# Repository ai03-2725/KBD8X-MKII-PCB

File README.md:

# KBD8X-MKII-PCB
This is the source for the PCB used in the [KBD8X MKII by KBDfans](https://kbdfans.com/collections/kbd8x-mkii/products/coming-soon-kbd8x-mkii-custom-mechanical-keyboard-kit).  

Please verify the conditions of the [license](https://github.com/ai03-2725/KBD8X-MKII-PCB/blob/master/LICENSE) before using.

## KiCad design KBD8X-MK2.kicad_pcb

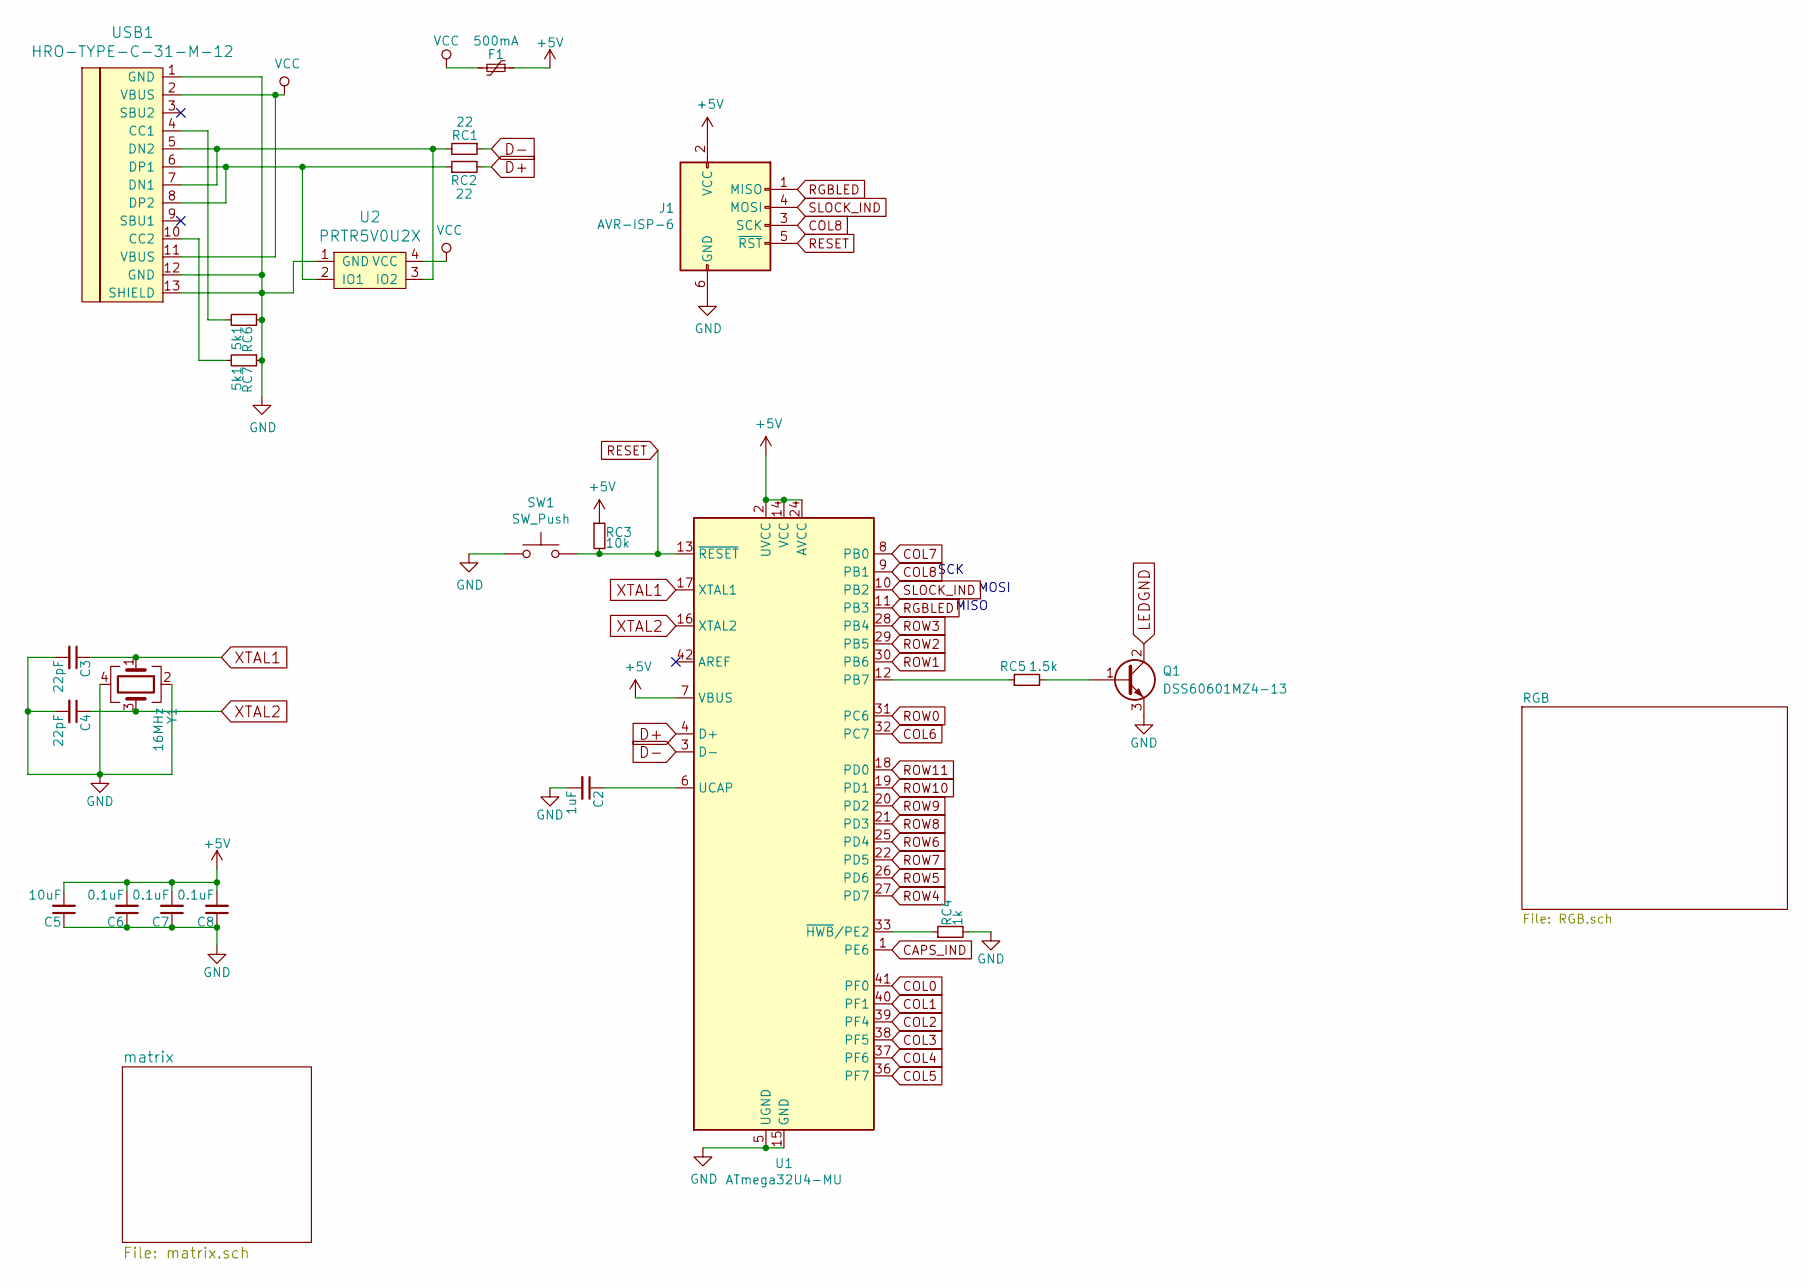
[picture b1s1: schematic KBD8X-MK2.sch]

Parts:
C2: 1uF; C_0603
C3, C4: 22pF; C_0603
C5: 10uF; C_0603
C6, C7, C8: 0.1uF; C_0603
F1: 500mA; Fuse_SMD1206_Wave
J1: AVR-ISP-6; Reset_Pretty-Mask
Q1: DSS60601MZ4-13; SOT-223-3_TabPin2
RC1, RC2: 22; R_0603
RC3: 10k; R_0603
RC4: 1k; R_0603
RC5: 1.5k; R_0603
RC6, RC7: 5k1; R_0603
SW1: SW_Push; SKQG-1155865
U1: ATmega32U4-MU; QFN-44-1EP_7x7mm_Pitch0.5mm
U2: PRTR5V0U2X; SOT143B
USB1: HRO-TYPE-C-31-M-12; HRO-TYPE-C-31-M-12-Assembly
Y1: 16MHz; Crystal_SMD_3225-4pin_3.2x2.5mm

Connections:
+5V: C5.2, C6.2, C7.2, C8.2, F1.1, J1.2 (VCC), RC3.1, U1.2 (UVCC), U1.7 (VBUS), U1.14 (VCC), U1.24 (AVCC), U1.34 (VCC), U1.44 (AVCC); also elsewhere on the board
CAPS_IND: U1.1 (PE6); also elsewhere on the board
COL0: U1.41 (PF0); also elsewhere on the board
COL1: U1.40 (PF1); also elsewhere on the board
COL2: U1.39 (PF4); also elsewhere on the board
COL3: U1.38 (PF5); also elsewhere on the board
COL4: U1.37 (PF6); also elsewhere on the board
COL5: U1.36 (PF7); also elsewhere on the board
COL6: U1.32 (PC7); also elsewhere on the board
COL7: U1.8 (PB0); also elsewhere on the board
COL8: J1.3 (SCK), U1.9 (PB1); also elsewhere on the board
D+: RC2.2, U1.4 (D+)
D-: RC1.1, U1.3 (D-)
GND: C2.2, C3.2, C4.2, C5.1, C6.1, C7.1, C8.1, J1.6 (GND), Q1.3 (E), RC4.2, RC6.1, RC7.1, SW1.1, U1.5 (UGND), U1.15 (GND), U1.23 (GND), U1.35 (GND), U1.43 (GND), U1.45 (GND), U2.1 (GND), USB1.1 (GND), USB1.12 (GND), USB1.13 (SHIELD), Y1.2, Y1.4; also elsewhere on the board
LEDGND: Q1.2 (C); also elsewhere on the board
unnamed: C2.1, U1.6 (UCAP)
unnamed: Q1.1 (B), RC5.2
unnamed: RC1.2, U2.3 (IO2), USB1.5 (DN2), USB1.7 (DN1)
unnamed: RC2.1, U2.2 (IO1), USB1.6 (DP1), USB1.8 (DP2)
unnamed: RC4.1, U1.33 (~HWB~/PE2)
unnamed: RC5.1, U1.12 (PB7)
unnamed: RC6.2, USB1.4 (CC1)
unnamed: RC7.2, USB1.10 (CC2)
RESET: J1.5 (~RST), RC3.2, SW1.2, U1.13 (~RESET)
RGBLED: J1.1 (MISO), U1.11 (PB3); also elsewhere on the board
ROW0: U1.31 (PC6); also elsewhere on the board
ROW1: U1.30 (PB6); also elsewhere on the board
ROW2: U1.29 (PB5); also elsewhere on the board
ROW3: U1.28 (PB4); also elsewhere on the board
ROW4: U1.27 (PD7); also elsewhere on the board
ROW5: U1.26 (PD6); also elsewhere on the board
ROW6: U1.25 (PD4); also elsewhere on the board
ROW7: U1.22 (PD5); also elsewhere on the board
ROW8: U1.21 (PD3); also elsewhere on the board
ROW9: U1.20 (PD2); also elsewhere on the board
ROW10: U1.19 (PD1); also elsewhere on the board
ROW11: U1.18 (PD0); also elsewhere on the board
SLOCK_IND: J1.4 (MOSI), U1.10 (PB2); also elsewhere on the board
VCC: F1.2, U2.4 (VCC), USB1.2 (VBUS), USB1.11 (VBUS)
XTAL1: C3.1, U1.17 (XTAL1), Y1.1
XTAL2: C4.1, U1.16 (XTAL2), Y1.3

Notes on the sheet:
MOSI
MISO
SCK

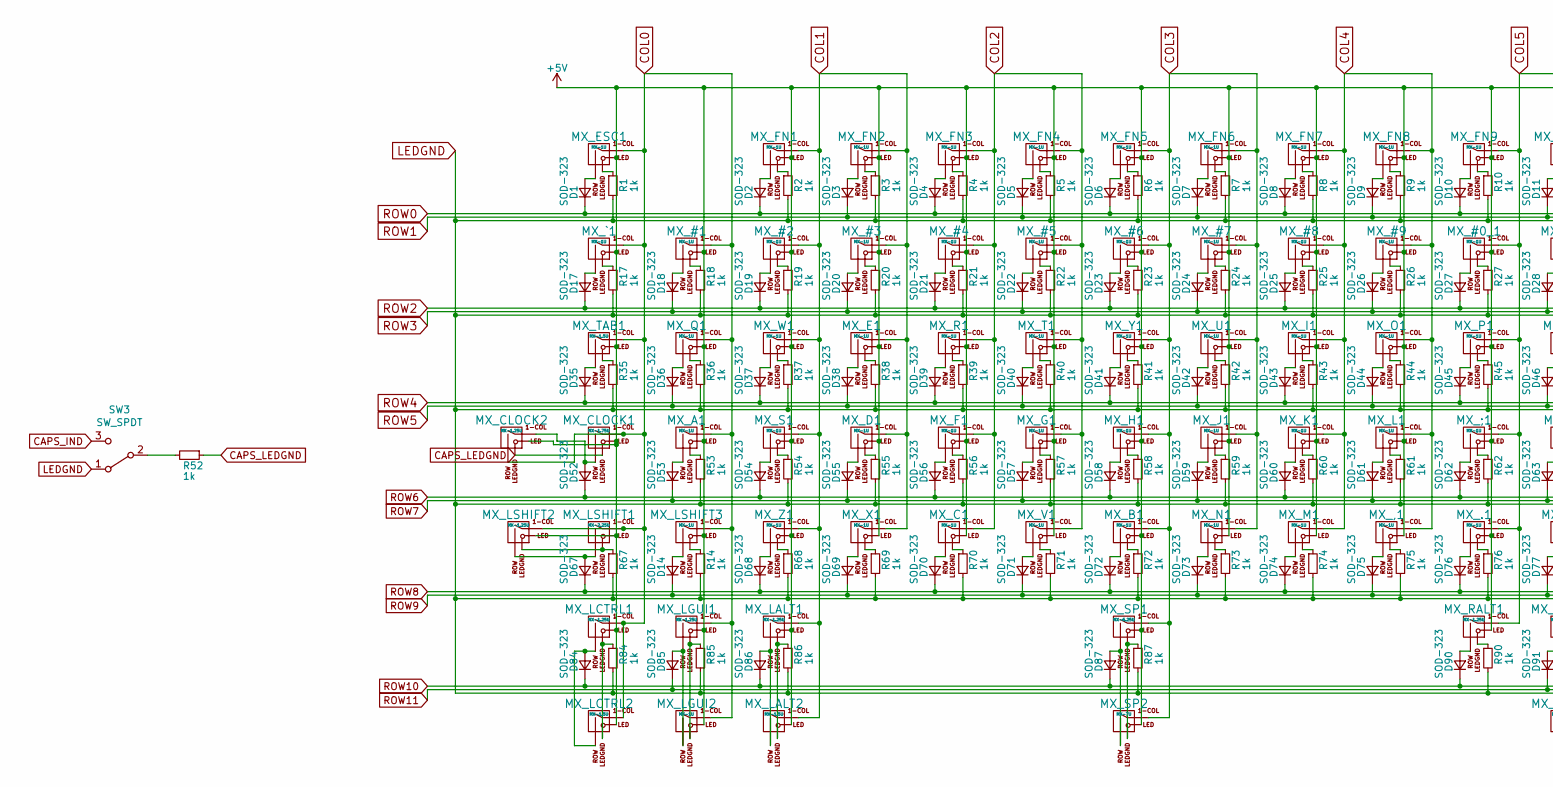
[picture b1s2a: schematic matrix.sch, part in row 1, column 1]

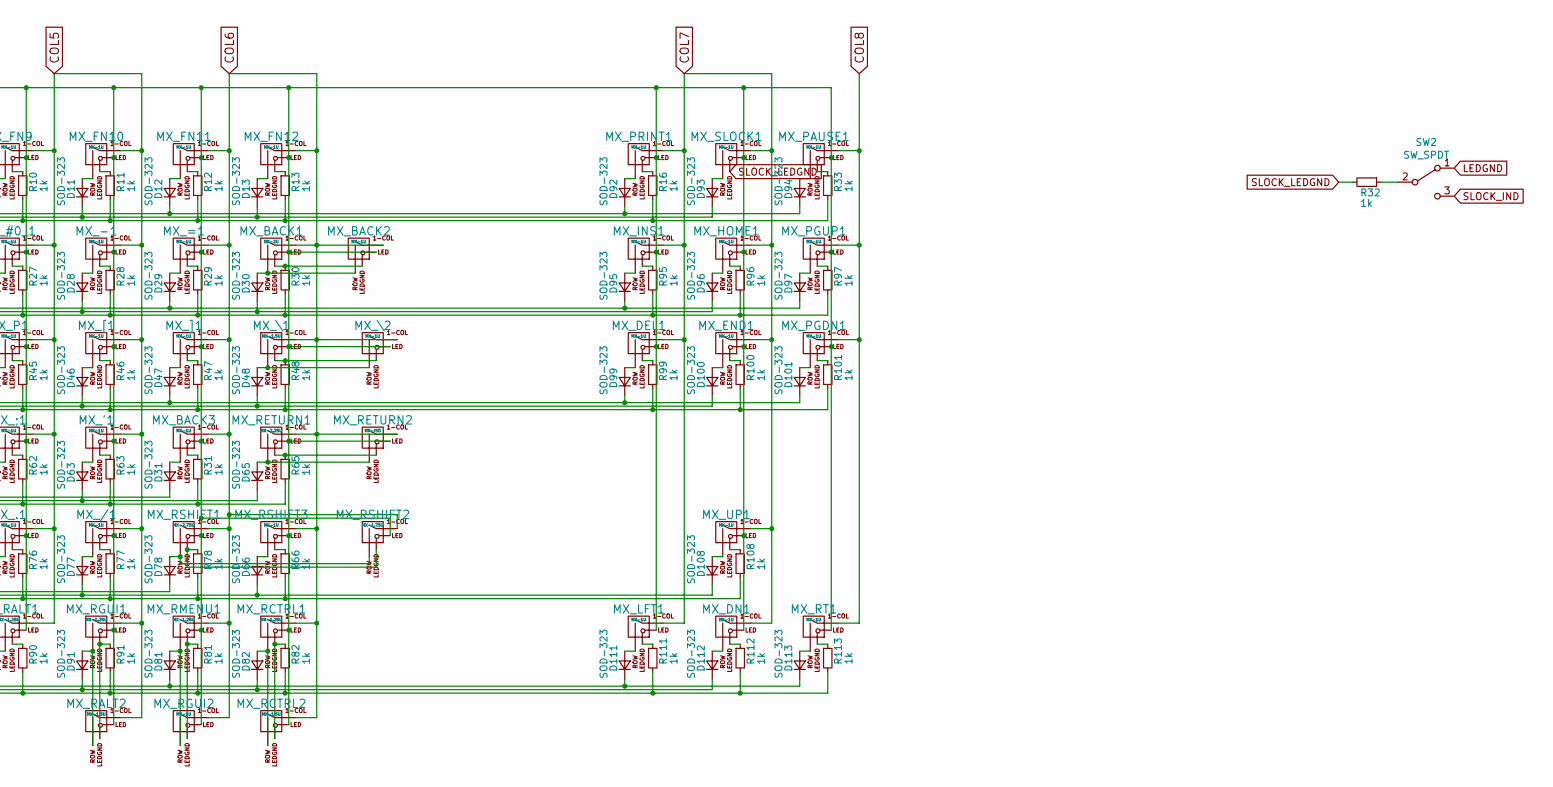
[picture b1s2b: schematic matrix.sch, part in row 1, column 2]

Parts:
D1, D2, D3, D4, D5, D6, D7, D8, D9, D10, D11, D12, D13, D14, D17, D18, D19, D20, D21, D22, D23, D24, D25, D26, D27, D28, D29, D30, D31, D35, D36, D37, D38, D39, D40, D41, D42, D43, D44, D45, D46, D47, D48, D52, D53, D54, D55, D56, D57, D58, D59, D60, D61, D62, D63, D65, D66, D67, D68, D69, D70, D71, D72, D73, D74, D75, D76, D77, D78, D81, D82, D84, D85, D86, D87, D90, D91, D92, D93, D94, D95, D96, D97, D99, D100, D101, D108, D111, D112, D113: SOD-323; D_SOD-123
MX_#0_1, MX_#1, MX_#2, MX_#3, MX_#4, MX_#5, MX_#6, MX_#7, MX_#8, MX_#9: MX-1U; MXOnly-1U
MX_'1: MX-1U; MXOnly-1U
MX_,1: MX-1U; MXOnly-1U
MX_-1: MX-1U; MXOnly-1U
MX_.1: MX-1U; MXOnly-1U
MX_/1: MX-1U; MXOnly-1U
MX_;1: MX-1U; MXOnly-1U
MX_=1: MX-1U; MXOnly-1U
MX_A1: MX-1U; MXOnly-1U
MX_B1: MX-1U; MXOnly-1U
MX_BACK1: MX-2U; MXOnly-2U
MX_BACK2, MX_BACK3: MX-1U; MXOnly-1U
MX_C1: MX-1U; MXOnly-1U
MX_CLOCK1: MX-1.75U; MXOnly-1.75U
MX_CLOCK2: MX-1.25U; MXOnly-1.25U-FLIPPED
MX_D1: MX-1U; MXOnly-1U
MX_DEL1: MX-1U; MXOnly-1U
MX_DN1: MX-1U; MXOnly-1U
MX_E1: MX-1U; MXOnly-1U
MX_END1: MX-1U; MXOnly-1U
MX_ESC1: MX-1U; MXOnly-1U
MX_F1: MX-1U; MXOnly-1U
MX_FN1, MX_FN2, MX_FN3, MX_FN4, MX_FN5, MX_FN6, MX_FN7, MX_FN8, MX_FN9, MX_FN10, MX_FN11, MX_FN12: MX-1U; MXOnly-1U
MX_G1: MX-1U; MXOnly-1U
MX_H1: MX-1U; MXOnly-1U
MX_HOME1: MX-1U; MXOnly-1U
MX_I1: MX-1U; MXOnly-1U
MX_INS1: MX-1U; MXOnly-1U
MX_J1: MX-1U; MXOnly-1U
MX_K1: MX-1U; MXOnly-1U
MX_L1: MX-1U; MXOnly-1U
MX_LALT1: MX-1.25U; MXOnly-1.25U
MX_LALT2: MX-1.5U; MXOnly-1.5U-FLIPPED
MX_LCTRL1: MX-1.25U; MXOnly-1.25U
MX_LCTRL2: MX-1.5U; MXOnly-1.5U-FLIPPED
MX_LFT1: MX-1U; MXOnly-1U
MX_LGUI1: MX-1.25U; MXOnly-1.25U
MX_LGUI2: MX-1U; MXOnly-1U-FLIPPED
MX_LSHIFT1: MX-2.25U; MXOnly-2.25U
MX_LSHIFT2: MX-1.25U; MXOnly-1.25U
MX_LSHIFT3: MX-1U; MXOnly-1U
MX_M1: MX-1U; MXOnly-1U
MX_N1: MX-1U; MXOnly-1U
MX_O1: MX-1U; MXOnly-1U
MX_P1: MX-1U; MXOnly-1U
MX_PAUSE1: MX-1U; MXOnly-1U
MX_PGDN1: MX-1U; MXOnly-1U
MX_PGUP1: MX-1U; MXOnly-1U
MX_PRINT1: MX-1U; MXOnly-1U
MX_Q1: MX-1U; MXOnly-1U
MX_R1: MX-1U; MXOnly-1U
MX_RALT1: MX-1.25U; MXOnly-1.25U
MX_RALT2: MX-1.5U; MXOnly-1.5U
MX_RCTRL1: MX-1.25U; MXOnly-1.25U-FLIPPED
MX_RCTRL2: MX-1.5U; MXOnly-1.5U
MX_RETURN1: MX-2.25U; MXOnly-2.25U
MX_RETURN2: MX-ISO; MXOnly-ISO-ROTATED-ReversedStabilizers
MX_RGUI1: MX-1.25U; MXOnly-1.25U-FLIPPED
MX_RGUI2: MX-1U; MXOnly-1U
MX_RMENU1: MX-1.25U; MXOnly-1.25U-FLIPPED
MX_RSHIFT1: MX-2.75U; MXOnly-2.75U
MX_RSHIFT2: MX-1.75U; MXOnly-1.75U
MX_RSHIFT3: MX-1U; MXOnly-1U
MX_RT1: MX-1U; MXOnly-1U
MX_S1: MX-1U; MXOnly-1U
MX_SLOCK1: MX-1U; MXOnly-1U
MX_SP1: MX-6.25U; MXOnly-6.25U-ReversedStabilizers
MX_SP2: MX-7U; MXOnly-7U-ReversedStabilizers
MX_T1: MX-1U; MXOnly-1U
MX_TAB1: MX-1.5U; MXOnly-1.5U
MX_U1: MX-1U; MXOnly-1U
MX_UP1: MX-1U; MXOnly-1U
MX_V1: MX-1U; MXOnly-1U
MX_W1: MX-1U; MXOnly-1U
MX_X1: MX-1U; MXOnly-1U
MX_Y1: MX-1U; MXOnly-1U
MX_Z1: MX-1U; MXOnly-1U
MX_[1: MX-1U; MXOnly-1U
MX_\1: MX-1.5U; MXOnly-1.5U
MX_\2: MX-1U; MXOnly-1U
MX_]1: MX-1U; MXOnly-1U
MX_`1: MX-1U; MXOnly-1U
R1, R2, R3, R4, R5, R6, R7, R8, R9, R10, R11, R12, R13, R14, R16, R17, R18, R19, R20, R21, R22, R23, R24, R25, R26, R27, R28, R29, R30, R31, R32, R33, R35, R36, R37, R38, R39, R40, R41, R42, R43, R44, R45, R46, R47, R48, R52, R53, R54, R55, R56, R57, R58, R59, R60, R61, R62, R63, R65, R66, R67, R68, R69, R70, R71, R72, R73, R74, R75, R76, R77, R78, R81, R82, R84, R85, R86, R87, R90, R91, R95, R96, R97, R99, R100, R101, R108, R111, R112, R113: 1k; R_0603
SW2, SW3: SW_SPDT; SW_SPDT_PCM12

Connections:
+5V: MX_#0_1.3 (LED), MX_#1.3 (LED), MX_#2.3 (LED), MX_#3.3 (LED), MX_#4.3 (LED), MX_#5.3 (LED), MX_#6.3 (LED), MX_#7.3 (LED), MX_#8.3 (LED), MX_#9.3 (LED), MX_'1.3 (LED), MX_,1.3 (LED), MX_-1.3 (LED), MX_.1.3 (LED), MX_/1.3 (LED), MX_;1.3 (LED), MX_=1.3 (LED), MX_A1.3 (LED), MX_B1.3 (LED), MX_BACK1.3 (LED), MX_BACK2.3 (LED), MX_BACK3.3 (LED), MX_C1.3 (LED), MX_CLOCK1.3 (LED), MX_CLOCK2.3 (LED), MX_D1.3 (LED), MX_DEL1.3 (LED), MX_DN1.3 (LED), MX_E1.3 (LED), MX_END1.3 (LED), MX_ESC1.3 (LED), MX_F1.3 (LED), MX_FN1.3 (LED), MX_FN2.3 (LED), MX_FN3.3 (LED), MX_FN4.3 (LED), MX_FN5.3 (LED), MX_FN6.3 (LED), MX_FN7.3 (LED), MX_FN8.3 (LED), MX_FN9.3 (LED), MX_FN10.3 (LED), MX_FN11.3 (LED), MX_FN12.3 (LED), MX_G1.3 (LED), MX_H1.3 (LED), MX_HOME1.3 (LED), MX_I1.3 (LED), MX_INS1.3 (LED), MX_J1.3 (LED), MX_K1.3 (LED), MX_L1.3 (LED), MX_LALT1.3 (LED), MX_LALT2.3 (LED), MX_LCTRL1.3 (LED), MX_LCTRL2.3 (LED), MX_LFT1.3 (LED), MX_LGUI1.3 (LED), MX_LGUI2.3 (LED), MX_LSHIFT1.3 (LED), MX_LSHIFT2.3 (LED), MX_LSHIFT3.3 (LED), MX_M1.3 (LED), MX_N1.3 (LED), MX_O1.3 (LED), MX_P1.3 (LED), MX_PAUSE1.3 (LED), MX_PGDN1.3 (LED), MX_PGUP1.3 (LED), MX_PRINT1.3 (LED), MX_Q1.3 (LED), MX_R1.3 (LED), MX_RALT1.3 (LED), MX_RALT2.3 (LED), MX_RCTRL1.3 (LED), MX_RCTRL2.3 (LED), MX_RETURN1.3 (LED), MX_RETURN2.3 (LED), MX_RGUI1.3 (LED), MX_RGUI2.3 (LED), MX_RMENU1.3 (LED), MX_RSHIFT1.3 (LED), MX_RSHIFT2.3 (LED), MX_RSHIFT3.3 (LED), MX_RT1.3 (LED), MX_S1.3 (LED), MX_SLOCK1.3 (LED), MX_SP1.3 (LED), MX_SP2.3 (LED), MX_T1.3 (LED), MX_TAB1.3 (LED), MX_U1.3 (LED), MX_UP1.3 (LED), MX_V1.3 (LED), MX_W1.3 (LED), MX_X1.3 (LED), MX_Y1.3 (LED), MX_Z1.3 (LED), MX_[1.3 (LED), MX_\1.3 (LED), MX_\2.3 (LED), MX_]1.3 (LED), MX_`1.3 (LED); also elsewhere on the board
CAPS_IND: SW3.3 (C); also elsewhere on the board
CAPS_LEDGND: MX_CLOCK1.4 (LEDGND), MX_CLOCK2.4 (LEDGND), R52.1
COL0: MX_#1.1 (COL), MX_A1.1 (COL), MX_CLOCK1.1 (COL), MX_CLOCK2.2 (ROW), MX_ESC1.1 (COL), MX_LCTRL1.1 (COL), MX_LCTRL2.1 (COL), MX_LGUI1.1 (COL), MX_LGUI2.1 (COL), MX_LSHIFT1.1 (COL), MX_LSHIFT2.1 (COL), MX_LSHIFT3.1 (COL), MX_Q1.1 (COL), MX_TAB1.1 (COL), MX_`1.1 (COL); also elsewhere on the board
COL1: MX_#2.1 (COL), MX_#3.1 (COL), MX_D1.1 (COL), MX_E1.1 (COL), MX_FN1.1 (COL), MX_FN2.1 (COL), MX_LALT1.1 (COL), MX_LALT2.1 (COL), MX_S1.1 (COL), MX_W1.1 (COL), MX_X1.1 (COL), MX_Z1.1 (COL); also elsewhere on the board
COL2: MX_#4.1 (COL), MX_#5.1 (COL), MX_C1.1 (COL), MX_F1.1 (COL), MX_FN3.1 (COL), MX_FN4.1 (COL), MX_G1.1 (COL), MX_R1.1 (COL), MX_T1.1 (COL), MX_V1.1 (COL); also elsewhere on the board
COL3: MX_#6.1 (COL), MX_#7.1 (COL), MX_B1.1 (COL), MX_FN5.1 (COL), MX_FN6.1 (COL), MX_H1.1 (COL), MX_J1.1 (COL), MX_N1.1 (COL), MX_SP1.1 (COL), MX_SP2.1 (COL), MX_U1.1 (COL), MX_Y1.1 (COL); also elsewhere on the board
COL4: MX_#8.1 (COL), MX_#9.1 (COL), MX_,1.1 (COL), MX_FN7.1 (COL), MX_FN8.1 (COL), MX_I1.1 (COL), MX_K1.1 (COL), MX_L1.1 (COL), MX_M1.1 (COL), MX_O1.1 (COL); also elsewhere on the board
COL5: MX_#0_1.1 (COL), MX_'1.1 (COL), MX_-1.1 (COL), MX_.1.1 (COL), MX_/1.1 (COL), MX_;1.1 (COL), MX_FN9.1 (COL), MX_FN10.1 (COL), MX_P1.1 (COL), MX_RALT1.1 (COL), MX_RALT2.1 (COL), MX_RGUI1.1 (COL), MX_[1.1 (COL); also elsewhere on the board
COL6: MX_=1.1 (COL), MX_BACK1.1 (COL), MX_BACK2.1 (COL), MX_BACK3.1 (COL), MX_FN11.1 (COL), MX_FN12.1 (COL), MX_RCTRL1.1 (COL), MX_RCTRL2.1 (COL), MX_RETURN1.1 (COL), MX_RETURN2.1 (COL), MX_RGUI2.1 (COL), MX_RMENU1.1 (COL), MX_RSHIFT1.1 (COL), MX_RSHIFT2.1 (COL), MX_RSHIFT3.1 (COL), MX_\1.1 (COL), MX_\2.1 (COL), MX_]1.1 (COL); also elsewhere on the board
COL7: MX_DEL1.1 (COL), MX_DN1.1 (COL), MX_END1.1 (COL), MX_HOME1.1 (COL), MX_INS1.1 (COL), MX_LFT1.1 (COL), MX_PRINT1.1 (COL), MX_SLOCK1.1 (COL), MX_UP1.1 (COL); also elsewhere on the board
COL8: MX_PAUSE1.1 (COL), MX_PGDN1.1 (COL), MX_PGUP1.1 (COL), MX_RT1.1 (COL); also elsewhere on the board
LEDGND: R1.2, R2.2, R3.2, R4.2, R5.2, R6.2, R7.2, R8.2, R9.2, R10.2, R11.2, R12.2, R13.2, R14.2, R16.2, R17.2, R18.2, R19.2, R20.2, R21.2, R22.2, R23.2, R24.2, R25.2, R26.2, R27.2, R28.2, R29.2, R30.2, R31.2, R33.2, R35.2, R36.2, R37.2, R38.2, R39.2, R40.2, R41.2, R42.2, R43.2, R44.2, R45.2, R46.2, R47.2, R48.2, R53.2, R54.2, R55.2, R56.2, R57.2, R58.2, R59.2, R60.2, R61.2, R62.2, R63.2, R65.2, R66.2, R67.2, R68.2, R69.2, R70.2, R71.2, R72.2, R73.2, R74.2, R75.2, R76.2, R77.2, R78.2, R81.2, R82.2, R84.2, R85.2, R86.2, R87.2, R90.2, R91.2, R95.2, R96.2, R97.2, R99.2, R100.2, R101.2, R108.2, R111.2, R112.2, R113.2, SW2.1 (A), SW3.1 (A); also elsewhere on the board
unnamed: D1.2 (A), MX_ESC1.2 (ROW)
unnamed: D2.2 (A), MX_FN1.2 (ROW)
unnamed: D3.2 (A), MX_FN2.2 (ROW)
unnamed: D4.2 (A), MX_FN3.2 (ROW)
unnamed: D5.2 (A), MX_FN4.2 (ROW)
unnamed: D6.2 (A), MX_FN5.2 (ROW)
unnamed: D7.2 (A), MX_FN6.2 (ROW)
unnamed: D8.2 (A), MX_FN7.2 (ROW)
unnamed: D9.2 (A), MX_FN8.2 (ROW)
unnamed: D10.2 (A), MX_FN9.2 (ROW)
unnamed: D11.2 (A), MX_FN10.2 (ROW)
unnamed: D12.2 (A), MX_FN11.2 (ROW)
unnamed: D13.2 (A), MX_FN12.2 (ROW)
unnamed: D14.2 (A), MX_LSHIFT3.2 (ROW)
unnamed: D17.2 (A), MX_`1.2 (ROW)
unnamed: D18.2 (A), MX_#1.2 (ROW)
unnamed: D19.2 (A), MX_#2.2 (ROW)
unnamed: D20.2 (A), MX_#3.2 (ROW)
unnamed: D21.2 (A), MX_#4.2 (ROW)
unnamed: D22.2 (A), MX_#5.2 (ROW)
unnamed: D23.2 (A), MX_#6.2 (ROW)
unnamed: D24.2 (A), MX_#7.2 (ROW)
unnamed: D25.2 (A), MX_#8.2 (ROW)
unnamed: D26.2 (A), MX_#9.2 (ROW)
unnamed: D27.2 (A), MX_#0_1.2 (ROW)
unnamed: D28.2 (A), MX_-1.2 (ROW)
unnamed: D29.2 (A), MX_=1.2 (ROW)
unnamed: D30.2 (A), MX_BACK1.2 (ROW), MX_BACK2.2 (ROW)
unnamed: D31.2 (A), MX_BACK3.2 (ROW)
unnamed: D35.2 (A), MX_TAB1.2 (ROW)
unnamed: D36.2 (A), MX_Q1.2 (ROW)
unnamed: D37.2 (A), MX_W1.2 (ROW)
unnamed: D38.2 (A), MX_E1.2 (ROW)
unnamed: D39.2 (A), MX_R1.2 (ROW)
unnamed: D40.2 (A), MX_T1.2 (ROW)
unnamed: D41.2 (A), MX_Y1.2 (ROW)
unnamed: D42.2 (A), MX_U1.2 (ROW)
unnamed: D43.2 (A), MX_I1.2 (ROW)
unnamed: D44.2 (A), MX_O1.2 (ROW)
unnamed: D45.2 (A), MX_P1.2 (ROW)
unnamed: D46.2 (A), MX_[1.2 (ROW)
unnamed: D47.2 (A), MX_]1.2 (ROW)
unnamed: D48.2 (A), MX_\1.2 (ROW), MX_\2.2 (ROW)
unnamed: D52.2 (A), MX_CLOCK1.2 (ROW), MX_CLOCK2.1 (COL)
unnamed: D53.2 (A), MX_A1.2 (ROW)
unnamed: D54.2 (A), MX_S1.2 (ROW)
unnamed: D55.2 (A), MX_D1.2 (ROW)
unnamed: D56.2 (A), MX_F1.2 (ROW)
unnamed: D57.2 (A), MX_G1.2 (ROW)
unnamed: D58.2 (A), MX_H1.2 (ROW)
unnamed: D59.2 (A), MX_J1.2 (ROW)
unnamed: D60.2 (A), MX_K1.2 (ROW)
unnamed: D61.2 (A), MX_L1.2 (ROW)
unnamed: D62.2 (A), MX_;1.2 (ROW)
unnamed: D63.2 (A), MX_'1.2 (ROW)
unnamed: D65.2 (A), MX_RETURN1.2 (ROW), MX_RETURN2.2 (ROW)
unnamed: D66.2 (A), MX_RSHIFT3.2 (ROW)
unnamed: D67.2 (A), MX_LSHIFT1.2 (ROW), MX_LSHIFT2.2 (ROW)
unnamed: D68.2 (A), MX_Z1.2 (ROW)
unnamed: D69.2 (A), MX_X1.2 (ROW)
unnamed: D70.2 (A), MX_C1.2 (ROW)
unnamed: D71.2 (A), MX_V1.2 (ROW)
unnamed: D72.2 (A), MX_B1.2 (ROW)
unnamed: D73.2 (A), MX_N1.2 (ROW)
unnamed: D74.2 (A), MX_M1.2 (ROW)
unnamed: D75.2 (A), MX_,1.2 (ROW)
unnamed: D76.2 (A), MX_.1.2 (ROW)
unnamed: D77.2 (A), MX_/1.2 (ROW)
unnamed: D78.2 (A), MX_RSHIFT1.2 (ROW), MX_RSHIFT2.2 (ROW)
unnamed: D81.2 (A), MX_RGUI2.2 (ROW), MX_RMENU1.2 (ROW)
unnamed: D82.2 (A), MX_RCTRL1.2 (ROW), MX_RCTRL2.2 (ROW)
unnamed: D84.2 (A), MX_LCTRL1.2 (ROW), MX_LCTRL2.2 (ROW)
unnamed: D85.2 (A), MX_LGUI1.2 (ROW), MX_LGUI2.2 (ROW)
unnamed: D86.2 (A), MX_LALT1.2 (ROW), MX_LALT2.2 (ROW)
unnamed: D87.2 (A), MX_SP1.2 (ROW), MX_SP2.2 (ROW)
unnamed: D90.2 (A), MX_RALT1.2 (ROW)
unnamed: D91.2 (A), MX_RALT2.2 (ROW), MX_RGUI1.2 (ROW)
unnamed: D92.2 (A), MX_PRINT1.2 (ROW)
unnamed: D93.2 (A), MX_SLOCK1.2 (ROW)
unnamed: D94.2 (A), MX_PAUSE1.2 (ROW)
unnamed: D95.2 (A), MX_INS1.2 (ROW)
unnamed: D96.2 (A), MX_HOME1.2 (ROW)
unnamed: D97.2 (A), MX_PGUP1.2 (ROW)
unnamed: D99.2 (A), MX_DEL1.2 (ROW)
unnamed: D100.2 (A), MX_END1.2 (ROW)
unnamed: D101.2 (A), MX_PGDN1.2 (ROW)
unnamed: D108.2 (A), MX_UP1.2 (ROW)
unnamed: D111.2 (A), MX_LFT1.2 (ROW)
unnamed: D112.2 (A), MX_DN1.2 (ROW)
unnamed: D113.2 (A), MX_RT1.2 (ROW)
unnamed: MX_#0_1.4 (LEDGND), R27.1
unnamed: MX_#1.4 (LEDGND), R18.1
unnamed: MX_#2.4 (LEDGND), R19.1
unnamed: MX_#3.4 (LEDGND), R20.1
unnamed: MX_#4.4 (LEDGND), R21.1
unnamed: MX_#5.4 (LEDGND), R22.1
unnamed: MX_#6.4 (LEDGND), R23.1
unnamed: MX_#7.4 (LEDGND), R24.1
unnamed: MX_#8.4 (LEDGND), R25.1
unnamed: MX_#9.4 (LEDGND), R26.1
unnamed: MX_'1.4 (LEDGND), R63.1
unnamed: MX_,1.4 (LEDGND), R75.1
unnamed: MX_-1.4 (LEDGND), R28.1
unnamed: MX_.1.4 (LEDGND), R76.1
unnamed: MX_/1.4 (LEDGND), R77.1
unnamed: MX_;1.4 (LEDGND), R62.1
unnamed: MX_=1.4 (LEDGND), R29.1
unnamed: MX_A1.4 (LEDGND), R53.1
unnamed: MX_B1.4 (LEDGND), R72.1
unnamed: MX_BACK1.4 (LEDGND), MX_BACK2.4 (LEDGND), R30.1
unnamed: MX_BACK3.4 (LEDGND), R31.1
unnamed: MX_C1.4 (LEDGND), R70.1
unnamed: MX_D1.4 (LEDGND), R55.1
unnamed: MX_DEL1.4 (LEDGND), R99.1
unnamed: MX_DN1.4 (LEDGND), R112.1
unnamed: MX_E1.4 (LEDGND), R38.1
unnamed: MX_END1.4 (LEDGND), R100.1
unnamed: MX_ESC1.4 (LEDGND), R1.1
unnamed: MX_F1.4 (LEDGND), R56.1
unnamed: MX_FN1.4 (LEDGND), R2.1
unnamed: MX_FN2.4 (LEDGND), R3.1
unnamed: MX_FN3.4 (LEDGND), R4.1
unnamed: MX_FN4.4 (LEDGND), R5.1
unnamed: MX_FN5.4 (LEDGND), R6.1
unnamed: MX_FN6.4 (LEDGND), R7.1
unnamed: MX_FN7.4 (LEDGND), R8.1
unnamed: MX_FN8.4 (LEDGND), R9.1
unnamed: MX_FN9.4 (LEDGND), R10.1
unnamed: MX_FN10.4 (LEDGND), R11.1
unnamed: MX_FN11.4 (LEDGND), R12.1
unnamed: MX_FN12.4 (LEDGND), R13.1
unnamed: MX_G1.4 (LEDGND), R57.1
unnamed: MX_H1.4 (LEDGND), R58.1
unnamed: MX_HOME1.4 (LEDGND), R96.1
unnamed: MX_I1.4 (LEDGND), R43.1
unnamed: MX_INS1.4 (LEDGND), R95.1
unnamed: MX_J1.4 (LEDGND), R59.1
unnamed: MX_K1.4 (LEDGND), R60.1
unnamed: MX_L1.4 (LEDGND), R61.1
unnamed: MX_LALT1.4 (LEDGND), MX_LALT2.4 (LEDGND), R86.1
unnamed: MX_LCTRL1.4 (LEDGND), MX_LCTRL2.4 (LEDGND), R84.1
unnamed: MX_LFT1.4 (LEDGND), R111.1
unnamed: MX_LGUI1.4 (LEDGND), MX_LGUI2.4 (LEDGND), R85.1
unnamed: MX_LSHIFT1.4 (LEDGND), MX_LSHIFT2.4 (LEDGND), R67.1
unnamed: MX_LSHIFT3.4 (LEDGND), R14.1
unnamed: MX_M1.4 (LEDGND), R74.1
unnamed: MX_N1.4 (LEDGND), R73.1
unnamed: MX_O1.4 (LEDGND), R44.1
unnamed: MX_P1.4 (LEDGND), R45.1
unnamed: MX_PAUSE1.4 (LEDGND), R33.1
unnamed: MX_PGDN1.4 (LEDGND), R101.1
unnamed: MX_PGUP1.4 (LEDGND), R97.1
unnamed: MX_PRINT1.4 (LEDGND), R16.1
unnamed: MX_Q1.4 (LEDGND), R36.1
unnamed: MX_R1.4 (LEDGND), R39.1
unnamed: MX_RALT1.4 (LEDGND), R90.1
unnamed: MX_RALT2.4 (LEDGND), MX_RGUI1.4 (LEDGND), R91.1
unnamed: MX_RCTRL1.4 (LEDGND), MX_RCTRL2.4 (LEDGND), R82.1
unnamed: MX_RETURN1.4 (LEDGND), MX_RETURN2.4 (LEDGND), R65.1
unnamed: MX_RGUI2.4 (LEDGND), MX_RMENU1.4 (LEDGND), R81.1
unnamed: MX_RSHIFT1.4 (LEDGND), MX_RSHIFT2.4 (LEDGND), R78.1
unnamed: MX_RSHIFT3.4 (LEDGND), R66.1
unnamed: MX_RT1.4 (LEDGND), R113.1
unnamed: MX_S1.4 (LEDGND), R54.1
unnamed: MX_SP1.4 (LEDGND), MX_SP2.4 (LEDGND), R87.1
unnamed: MX_T1.4 (LEDGND), R40.1
unnamed: MX_TAB1.4 (LEDGND), R35.1
unnamed: MX_U1.4 (LEDGND), R42.1
unnamed: MX_UP1.4 (LEDGND), R108.1
unnamed: MX_V1.4 (LEDGND), R71.1
unnamed: MX_W1.4 (LEDGND), R37.1
unnamed: MX_X1.4 (LEDGND), R69.1
unnamed: MX_Y1.4 (LEDGND), R41.1
unnamed: MX_Z1.4 (LEDGND), R68.1
unnamed: MX_[1.4 (LEDGND), R46.1
unnamed: MX_\1.4 (LEDGND), MX_\2.4 (LEDGND), R48.1
unnamed: MX_]1.4 (LEDGND), R47.1
unnamed: MX_`1.4 (LEDGND), R17.1
unnamed: R32.1, SW2.2 (B)
unnamed: R52.2, SW3.2 (B)
ROW0: D1.1 (K), D2.1 (K), D4.1 (K), D6.1 (K), D8.1 (K), D10.1 (K), D12.1 (K), D92.1 (K), D94.1 (K); also elsewhere on the board
ROW1: D3.1 (K), D5.1 (K), D7.1 (K), D9.1 (K), D11.1 (K), D13.1 (K), D93.1 (K); also elsewhere on the board
ROW2: D17.1 (K), D19.1 (K), D21.1 (K), D23.1 (K), D25.1 (K), D27.1 (K), D29.1 (K), D95.1 (K), D97.1 (K); also elsewhere on the board
ROW3: D18.1 (K), D20.1 (K), D22.1 (K), D24.1 (K), D26.1 (K), D28.1 (K), D30.1 (K), D96.1 (K); also elsewhere on the board
ROW4: D35.1 (K), D37.1 (K), D39.1 (K), D41.1 (K), D43.1 (K), D45.1 (K), D47.1 (K), D99.1 (K), D101.1 (K); also elsewhere on the board
ROW5: D36.1 (K), D38.1 (K), D40.1 (K), D42.1 (K), D44.1 (K), D46.1 (K), D48.1 (K), D100.1 (K); also elsewhere on the board
ROW6: D31.1 (K), D52.1 (K), D54.1 (K), D56.1 (K), D58.1 (K), D60.1 (K), D62.1 (K); also elsewhere on the board
ROW7: D53.1 (K), D55.1 (K), D57.1 (K), D59.1 (K), D61.1 (K), D63.1 (K), D65.1 (K); also elsewhere on the board
ROW8: D67.1 (K), D68.1 (K), D70.1 (K), D72.1 (K), D74.1 (K), D76.1 (K), D78.1 (K); also elsewhere on the board
ROW9: D14.1 (K), D66.1 (K), D69.1 (K), D71.1 (K), D73.1 (K), D75.1 (K), D77.1 (K), D108.1 (K); also elsewhere on the board
ROW10: D81.1 (K), D84.1 (K), D86.1 (K), D87.1 (K), D90.1 (K), D111.1 (K), D113.1 (K); also elsewhere on the board
ROW11: D82.1 (K), D85.1 (K), D91.1 (K), D112.1 (K); also elsewhere on the board
SLOCK_IND: SW2.3 (C); also elsewhere on the board
SLOCK_LEDGND: MX_SLOCK1.4 (LEDGND), R32.2

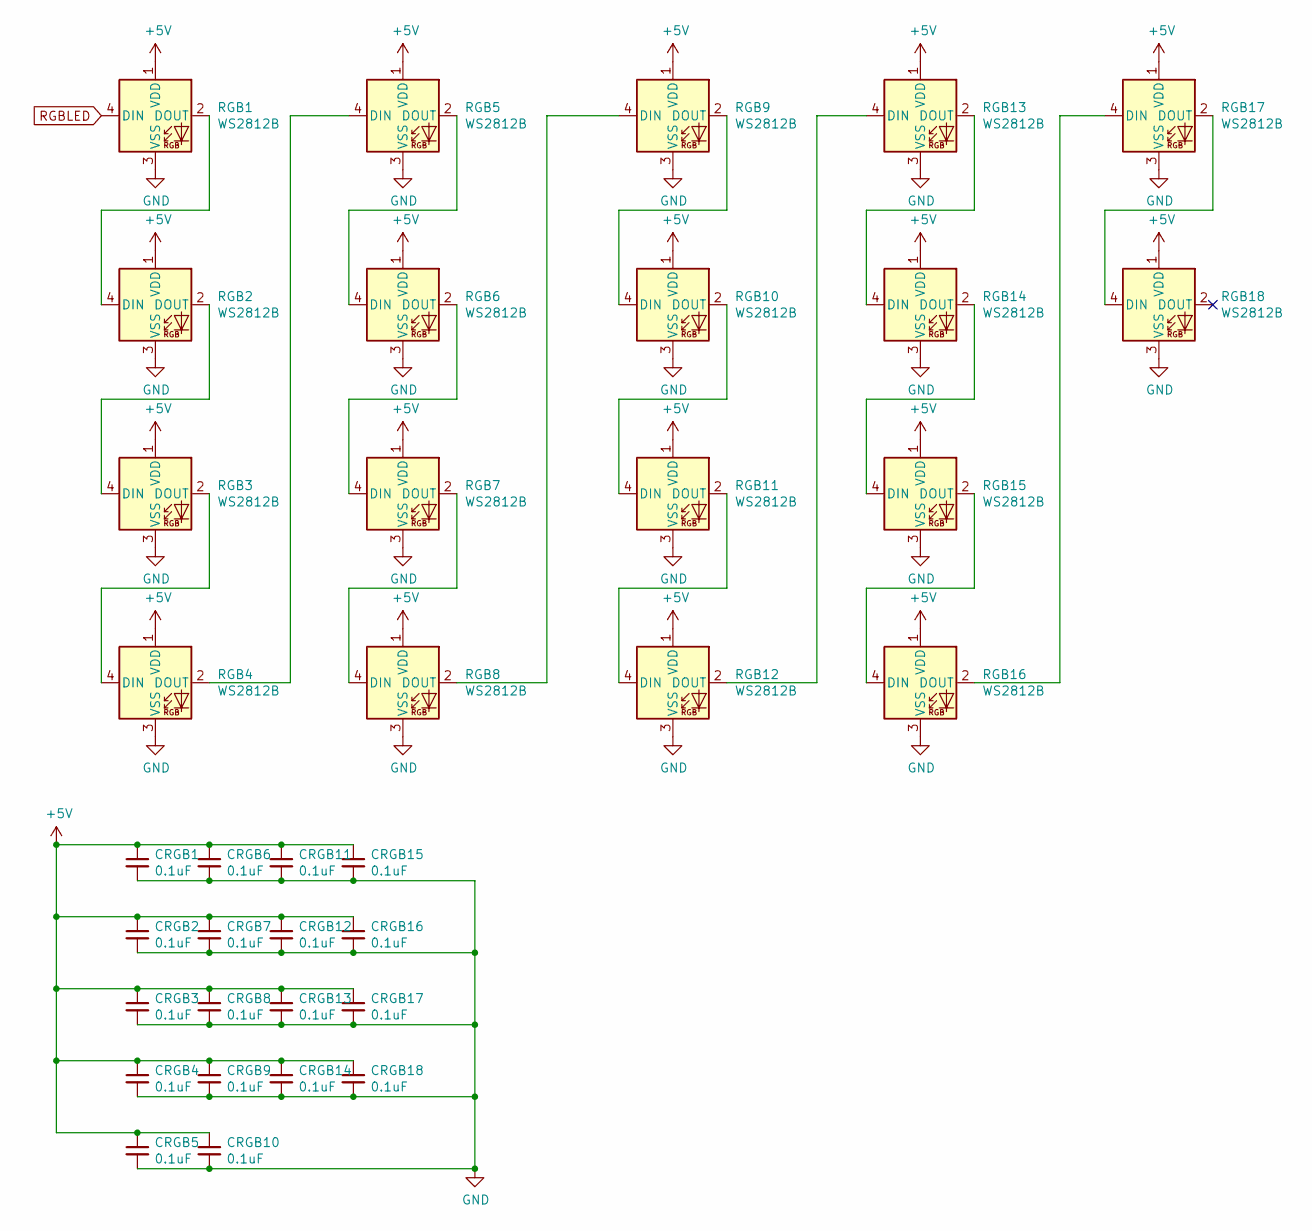
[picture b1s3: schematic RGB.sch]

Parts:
CRGB1, CRGB2, CRGB3, CRGB4, CRGB5, CRGB6, CRGB7, CRGB8, CRGB9, CRGB10, CRGB11, CRGB12, CRGB13, CRGB14, CRGB15, CRGB16, CRGB17, CRGB18: 0.1uF; C_0603
RGB1, RGB2, RGB3, RGB4, RGB5, RGB6, RGB7, RGB8, RGB9, RGB10, RGB11, RGB12, RGB13, RGB14, RGB15, RGB16, RGB17, RGB18: WS2812B; LED_WS2812B-PLCC4

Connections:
+5V: CRGB1.1, CRGB2.1, CRGB3.1, CRGB4.1, CRGB5.1, CRGB6.1, CRGB7.1, CRGB8.1, CRGB9.1, CRGB10.1, CRGB11.1, CRGB12.1, CRGB13.1, CRGB14.1, CRGB15.1, CRGB16.1, CRGB17.1, CRGB18.1, RGB1.1 (VDD), RGB2.1 (VDD), RGB3.1 (VDD), RGB4.1 (VDD), RGB5.1 (VDD), RGB6.1 (VDD), RGB7.1 (VDD), RGB8.1 (VDD), RGB9.1 (VDD), RGB10.1 (VDD), RGB11.1 (VDD), RGB12.1 (VDD), RGB13.1 (VDD), RGB14.1 (VDD), RGB15.1 (VDD), RGB16.1 (VDD), RGB17.1 (VDD), RGB18.1 (VDD); also elsewhere on the board
GND: CRGB1.2, CRGB2.2, CRGB3.2, CRGB4.2, CRGB5.2, CRGB6.2, CRGB7.2, CRGB8.2, CRGB9.2, CRGB10.2, CRGB11.2, CRGB12.2, CRGB13.2, CRGB14.2, CRGB15.2, CRGB16.2, CRGB17.2, CRGB18.2, RGB1.3 (VSS), RGB2.3 (VSS), RGB3.3 (VSS), RGB4.3 (VSS), RGB5.3 (VSS), RGB6.3 (VSS), RGB7.3 (VSS), RGB8.3 (VSS), RGB9.3 (VSS), RGB10.3 (VSS), RGB11.3 (VSS), RGB12.3 (VSS), RGB13.3 (VSS), RGB14.3 (VSS), RGB15.3 (VSS), RGB16.3 (VSS), RGB17.3 (VSS), RGB18.3 (VSS); also elsewhere on the board
unnamed: RGB1.2 (DOUT), RGB2.4 (DIN)
unnamed: RGB2.2 (DOUT), RGB3.4 (DIN)
unnamed: RGB3.2 (DOUT), RGB4.4 (DIN)
unnamed: RGB4.2 (DOUT), RGB5.4 (DIN)
unnamed: RGB5.2 (DOUT), RGB6.4 (DIN)
unnamed: RGB6.2 (DOUT), RGB7.4 (DIN)
unnamed: RGB7.2 (DOUT), RGB8.4 (DIN)
unnamed: RGB8.2 (DOUT), RGB9.4 (DIN)
unnamed: RGB10.2 (DOUT), RGB11.4 (DIN)
unnamed: RGB9.2 (DOUT), RGB10.4 (DIN)
unnamed: RGB11.2 (DOUT), RGB12.4 (DIN)
unnamed: RGB12.2 (DOUT), RGB13.4 (DIN)
unnamed: RGB13.2 (DOUT), RGB14.4 (DIN)
unnamed: RGB14.2 (DOUT), RGB15.4 (DIN)
unnamed: RGB15.2 (DOUT), RGB16.4 (DIN)
unnamed: RGB16.2 (DOUT), RGB17.4 (DIN)
unnamed: RGB17.2 (DOUT), RGB18.4 (DIN)
RGBLED: RGB1.4 (DIN); also elsewhere on the board

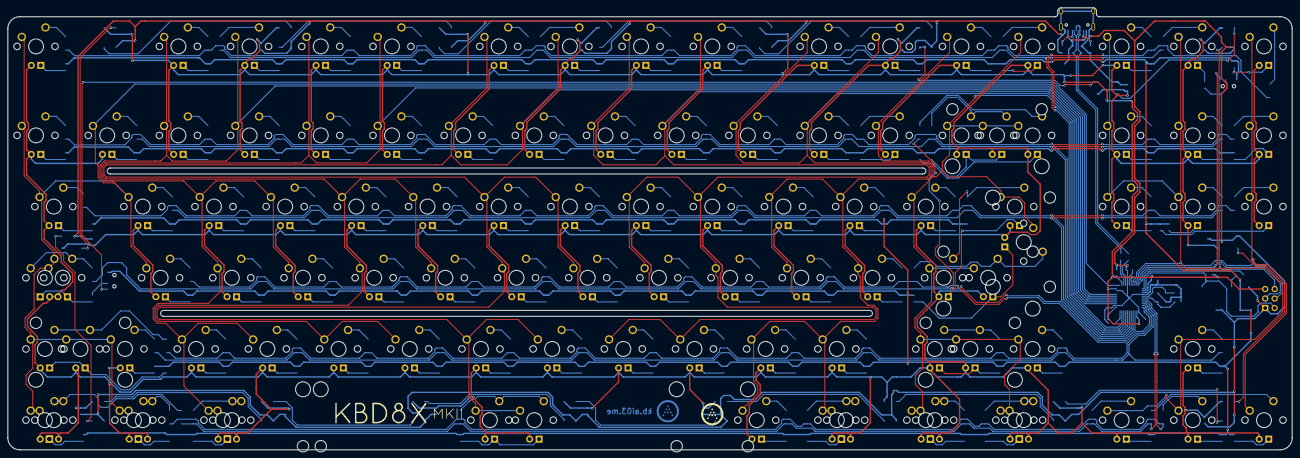
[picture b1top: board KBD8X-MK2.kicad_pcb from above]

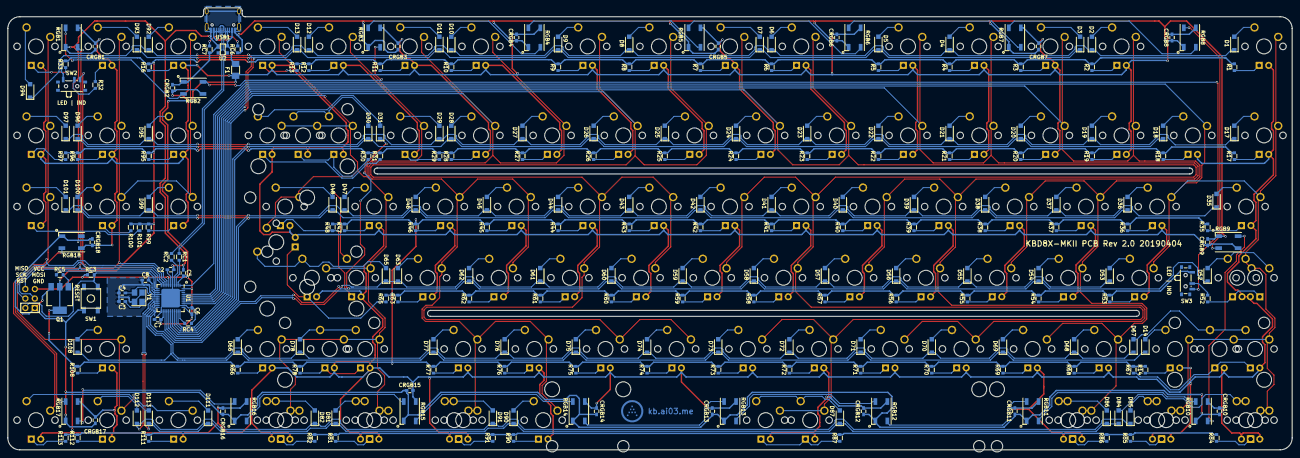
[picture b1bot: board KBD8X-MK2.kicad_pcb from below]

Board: 2 copper layers, 343.7 x 118.3 mm, 343 parts (240 on the bottom side), 240 nets.

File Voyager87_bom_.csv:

Component,Description,Part,References,Value,Footprint,Quantity Per PCB,Datasheet,Field8,Field4,Field7,Field6,Field5
1,,MX-1U,"BS1-2 BS2 MX_#0_1 MX_#1 MX_#2 MX_#3 MX_#4 MX_#5 MX_#6 MX_#7 MX_#8 MX_#9 MX_'1 MX_,1 MX_-1 MX_.1 MX_/1 MX_;1 MX_=1 MX_A1 MX_B1 MX_C1 MX_D1 MX_DOWN1 MX_E1 MX_ESC1 MX_EX1 MX_EX2 MX_EX3 MX_EX4 MX_F1 MX_FN1 MX_FN2 MX_FN3 MX_FN4 MX_FN5 MX_FN6 MX_FN7 MX_FN8 MX_FN9 MX_FN10 MX_FN11 MX_FN12 MX_G1 MX_H1 MX_I1 MX_J1 MX_K1 MX_L1 MX_LEFT1 MX_M1 MX_N1 MX_NUM1 MX_NUM2 MX_NUM3 MX_NUM4 MX_NUM5 MX_NUM6 MX_NUM7 MX_NUM8 MX_NUM9 MX_NUM10 MX_NUM11 MX_NUM12 MX_NUM13 MX_NUM14 MX_NUM15 MX_NUM16 MX_NUM17 MX_NUM18 MX_NUM19 MX_NUM20 MX_NUM21 MX_NUM22 MX_NUM23 MX_NUM24 MX_O1 MX_P1 MX_Q1 MX_R1 MX_RESET1 MX_RIGHT1 MX_S1 MX_T1 MX_U1 MX_UP1 MX_V1 MX_W1 MX_X1 MX_Y1 MX_Z1 MX_[1 MX_]1 MX_`1",MX-1U,MX-1U,94,,,,,,
2,,MX-2U,BS1-1,MX-2U,MX-2U,1,,,,,,
3,Unpolarized capacitor,C_Small,C6 C7 C8,0.1uF,C_0603,3,,,,,,
4,Unpolarized capacitor,C_Small,C2 C5,1uF,C_0603,2,,,,,,
5,Unpolarized capacitor,C_Small,C3 C4,22pF,C_0603,2,,,,,,
6,,MX-1.25U,CL1-2,MX-1.25U,MX-1.25U-FLIPPED,1,,,,,,
7,,MX-1.75U,CL1-1,MX-1.75U,MX-1.75U,1,,,,,,
8,"Diode, small symbol",D_Small,D1 D2 D3 D4 D5 D6 D7 D8 D9 D10 D11 D12 D13 D14 D15 D16 D17 D18 D19 D20 D21 D22 D23 D24 D25 D26 D27 D28 D29 D30 D31 D32 D33 D35 D36 D37 D38 D39 D40 D41 D42 D43 D44 D45 D46 D47 D48 D52 D53 D54 D55 D56 D57 D58 D59 D60 D61 D62 D63 D65 D66 D67 D68 D69 D70 D71 D72 D73 D74 D75 D76 D77 D78 D80 D81 D82 D83 D84 D85 D86 D87 D89 D90 D91 D92 D93 D94 D95 D96 D97 D98 D99 D100 D101 D102 D103 D104 D105 D106 D107 D108 D109 D110 D111 D112 D113 D114,SOD-323,D_SOD-123,107,,,,,,
9,"resettable fuse, polymeric positive temperature coefficient (PPTC), small symbol",Polyfuse_Small,F1,500mA,Fuse_SMD1206_Reflow,1,,,,,,
10,Atmel 6-pin ISP connector,AVR-ISP-6,J1,AVR-ISP-6,Reset_Pretty-Mask,1, ~,,,,,
11,,MX-1U,LM1-1,MX-1.25U,MX-1.25U,1,,,,,,
12,,MX-1.25U,LM2-1 LM3-1,MX-1.25U,MX-1.25U,2,,,,,,
13,,MX-1.5U,LM1-2 RM1-2 RM3-2,MX-1.5U,MX-1.5U-FLIPPED,3,,,,,,
14,,MX-1.5U,LM3-2 MX_TAB1 MX_\1,MX-1.5U,MX-1.5U,3,,,,,,
15,,MX-2.25U,LS1-1 MX_RETURN1,MX-2.25U,MX-2.25U,2,,,,,,
16,,MX-1U,MX_RSHIFT1,MX-1.75U,MX-1.75U,1,,,,,,
17,,MX-1U,MX_NUMEXT2 MX_NUMEXT4 MX_NUMEXT5,MX-2U,MX-2U-ReversedStabilizers,3,,,,,,
18,Transistor NPN (general),Q_NPN_BCE,Q1,DSS60601MZ4-13,SOT-223-3_TabPin2,1,,,,,,
19,"Resistor, small symbol",R_Small,R1 R2 R3 R4 R5 R6 R7 R8 R9 R10 R11 R12 R13 R14 R15 R16 R17 R18 R19 R20 R21 R22 R23 R24 R25 R26 R27 R28 R29 R30 R31 R32 R33 R34 R35 R36 R37 R38 R39 R40 R41 R42 R43 R44 R45 R46 R47 R48 R49 R50 R52 R53 R54 R55 R56 R57 R58 R59 R60 R61 R62 R63 R65 R66 R67 R68 R69 R70 R71 R72 R73 R74 R75 R76 R77 R78 R80 R81 R82 R83 R84 R85 R86 R87 R89 R90 R91 R95 R96 R97 R98 R99 R100 R101 R102 R103 R104 R105 R106 R107 R108 R109 R110 R111 R112 R113 R114 RC4,1k,R_0603,108,,,,,,
20,"Resistor, small symbol",R_Small,RC5,1.5k,R_0603,1,,,,,,
21,"Resistor, small symbol",R_Small,RC3,10k,R_0603,1,,,,,,
22,"Resistor, small symbol",R_Small,RC1 RC2,22,R_0603,2,,,,,,
23,"Resistor, small symbol",R_Small,RC6 RC7,5k1,R_0603,2,,,,,,
24,,MX-1.25U,RM1-1 RM2-1 RM3-1,MX-1U,MX-1U,3,,,,,,
25,,MX-6.25U,SP1,MX-6.25U,MX-6.25U-ReversedStabilizers,1,,,,,,
26,,MX-7U,SP2,MX-7U,MX-7U-ReversedStabilizers,1,,,,,,
27,"Push button switch, generic, two pins",SW_Push,SW1,SW_Push,SKQG-1155865,1,,,,,,
28,"16MHz, 64kB Flash, 4kB SRAM, 2kB EEPROM, USB 2.0, QFN-64",AT90USB1286-MU,U1,AT90USB1286-AU,QFN-64-1EP_9x9mm_Pitch0.5mm,1,8.69 USD,AT90USB1286-AU,TQFP-64 Microchip,Good,Embedded microcontroller AT90USB1286-AU TQFP 64 _14x14_ Microchip Technology 8-Bit 16 MHz I/O number 48,Microchip
29,,PRTR5V0U2X,U2,PRTR5V0U2X,SOT143B,1,,,,,,
30,,HRO-TYPE-C-31-M-12,USB1,HRO-TYPE-C-31-M-12,HRO-TYPE-C-31-M-12-Assembly,1,,,,,,
31,"Four pin crystal (GND on pins 2 and 4), e.g. in SMD package",Crystal_GND24,Y1,16MHz,Crystal_SMD_3225-4pin_3.2x2.5mm,1,,,,,,
,,,,,,,,,,,,
,,,,,,,,,,,,
,,,,,,,,,,,,
,,,,,,,,,,,,
,,,,,,,,,,,,
Component Groups:,31,,,,,,,,,,,
Component Count:,353,,,,,,,,,,,
Fitted Components:,353,,,,,,,,,,,
Number of PCBs:,1,,,,,,,,,,,
Total components:,353,,,,,,,,,,,
Schematic Version:,,,,,,,,,,,,
Schematic Date:,,,,,,,,,,,,
BoM Date:,1/27/2019 3:01,,,,,,,,,,,
Schematic Source:,,,,,,,,,,,,
KiCad Version:,Eeschema (5.0.0),,,,,,,,,,,

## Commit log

2019-02-07 Add submods
2019-02-07 Temporary progress save
2019-02-11 Progress
2019-07-27 Working copy
2019-07-27 Begin readme
2019-07-27 Add render
2019-07-27 Link to license file
2019-07-27 Swap license to make it a bit more usable
2019-07-27 Swap license until decided what to actually license it under
